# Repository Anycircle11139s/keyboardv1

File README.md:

# keyboardv1
For hack club stasis, I have to journal a lot, and when I journal, I'm locked in, I just keep on typing and typing until I realise that my hands ache like hell because of my uncomfortable keyboard. Because of this, I decided to make myself a customisable 65% keyboard that I can use for playing games (I can customise the keys and make different modes for what I'm doing), journal and all my other typing needs. I created a keyboard matrix for the schematic and placed all my keys into a specific format in the pcb along with making some stablisation holes for space bars and other keycaps. I also added some tuff af silkscreen to the PCB. For the case, I designed a simple, sleek case which surround the keyboard and has no lid. I made it simplistic but added some small design additions so the keyboard wouldn't get to boring. I also added a small slot to the case of my split keyboard which I can use to attach modules whihc I can design in the future. Overall I am really proud of what I made and can't wait to build it irl.

<br>

<br>

<br>

<br>

<br>

<br>

<br>

<br>
<br>
<br>

BOM:
<br>
<br>

|Name                             |Purpose                           |Quantity|Total Cost (USD)|Link                                                                                                                                                                                                                                                                                                                                                                                                                                                                                                                                                                                                                                          |Distributor    |
|---------------------------------|----------------------------------|--------|----------------|----------------------------------------------------------------------------------------------------------------------------------------------------------------------------------------------------------------------------------------------------------------------------------------------------------------------------------------------------------------------------------------------------------------------------------------------------------------------------------------------------------------------------------------------------------------------------------------------------------------------------------------------|---------------|
|case                             |the case for the keyboard         |1       |10.00           |                                                                                                                                                                                                                                                                                                                                                                                                                                                                                                                                                                                                                                              |printing legion|
|PCB                              |the pcb for the board             |1       |27.84           |                                                                                                                                                                                                                                                                                                                                                                                                                                                                                                                                                                                                                                              |jlcpcb         |
|1n4148 diodes                    |the diodes for keyboard matrix    |100     |2.84            |https://www.aliexpress.com/item/1005011766943016.html?spm=a2g0o.productlist.main.7.6b3366c9XO8nET&algo_pvid=4686ff8b-01ef-4d59-aece-2ba6a6420e8b&algo_exp_id=4686ff8b-01ef-4d59-aece-2ba6a6420e8b-6&pdp_ext_f=%7B%22order%22%3A%22159%22%2C%22eval%22%3A%221%22%2C%22fromPage%22%3A%22search%22%7D&pdp_npi=6%40dis%21USD%212.96%212.84%21%21%2120.10%2119.30%21%402101d97817776923407452272e1e3a%2112000056498191665%21sea%21AU%217402515296%21X%211%210%21n_tag%3A-29919%3Bd%3Aef1e07f3%3Bm03_new_user%3A-29895&curPageLogUid=WxqQIHnQBOvN&utparam-url=scene%3Asearch%7Cquery_from%3A%7Cx_object_id%3A1005011766943016%7C_p_origin_prod%3A   |ali express    |
|raspberry pi pico h              |the microconrtoller devboard thing|1       |3.00            |https://www.aliexpress.com/item/1005009844027732.html?spm=a2g0o.productlist.main.13.4827apCCapCCqF&utparam-url=scene%3Asearch%7Cquery_from%3Apc_back_same_best%7Cx_object_id%3A1005009844027732%7C_p_origin_prod%3A&algo_pvid=c51c447d-b00d-4d3c-9df1-87a988eed2e9&algo_exp_id=c51c447d-b00d-4d3c-9df1-87a988eed2e9&pdp_ext_f=%7B%22order%22%3A%221119%22%2C%22fromPage%22%3A%22search%22%7D&pdp_npi=6%40dis%21USD%216.57%212.98%21%21%2144.62%2120.23%21%40210328c017776922501718063e1b4c%2112000050339370579%21sea%21AU%217402515296%21X%211%210%21n_tag%3A-29919%3Bd%3Aef1e07f3%3Bm03_new_user%3A-29895%3BpisId%3A5000000206134117         |ali express    |
|Durock Clear Screw-In Stabilizers|stabilizers for space bar         |1       |7.00            |https://www.aliexpress.com/item/1005007236845004.html?spm=a2g0o.productlist.main.3.1898ase7ase7JM&algo_pvid=5806a8f2-4c32-4dd2-bbc1-282acfa51f49&algo_exp_id=5806a8f2-4c32-4dd2-bbc1-282acfa51f49-2&pdp_ext_f=%7B%22order%22%3A%22126%22%2C%22eval%22%3A%221%22%2C%22fromPage%22%3A%22search%22%7D&pdp_npi=6%40dis%21USD%216.35%216.35%21%21%216.35%216.35%21%402101e81117776932688596724e0a2a%2112000039909995531%21sea%21AU%217402515296%21X%211%210%21n_tag%3A-29919%3Bd%3Aef1e07f3%3Bm03_new_user%3A-29895&curPageLogUid=cq3Hpwq6BscB&utparam-url=scene%3Asearch%7Cquery_from%3A%7Cx_object_id%3A1005007236845004%7C_p_origin_prod%3A     |ali express    |
|blue gradient keycaps            |switch covers                     |1       |16.55           |https://www.aliexpress.com/item/1005009032705520.html?spm=a2g0o.productlist.main.2.7fe21aK91aK965&algo_pvid=6edcfeac-de3a-448c-b303-d10f2607c087&algo_exp_id=6edcfeac-de3a-448c-b303-d10f2607c087-1&pdp_ext_f=%7B%22order%22%3A%2213%22%2C%22eval%22%3A%221%22%2C%22fromPage%22%3A%22search%22%7D&pdp_npi=6%40dis%21USD%2122.07%2116.55%21%21%21149.93%21112.45%21%402101d49617776918006226446e4027%2112000047655880268%21sea%21AU%217402515296%21X%211%210%21n_tag%3A-29919%3Bd%3Aef1e07f3%3Bm03_new_user%3A-29895&curPageLogUid=8Wpnbc57EDZi&utparam-url=scene%3Asearch%7Cquery_from%3A%7Cx_object_id%3A1005009032705520%7C_p_origin_prod%3A|ali express    |
|switches                         |the buttons in keyboard           |90      |35.69           |https://www.aliexpress.com/item/1005009496269008.html?spm=a2g0o.productlist.main.2.7e02fM5MfM5MXw&algo_pvid=59a365f0-2600-4815-a56b-d0a97a5b4dbd&algo_exp_id=59a365f0-2600-4815-a56b-d0a97a5b4dbd-1&pdp_ext_f=%7B%22order%22%3A%22106%22%2C%22eval%22%3A%221%22%2C%22fromPage%22%3A%22search%22%7D&pdp_npi=6%40dis%21USD%2122.99%2119.54%21%21%2122.99%2119.54%21%402101e83017776915737453434ebe85%2112000053392741002%21sea%21AU%217402515296%21X%211%210%21n_tag%3A-29919%3Bd%3Aef1e07f3%3Bm03_new_user%3A-29895&curPageLogUid=lkGMG2pIpivm&utparam-url=scene%3Asearch%7Cquery_from%3A%7Cx_object_id%3A1005009496269008%7C_p_origin_prod%3A |ali express    |

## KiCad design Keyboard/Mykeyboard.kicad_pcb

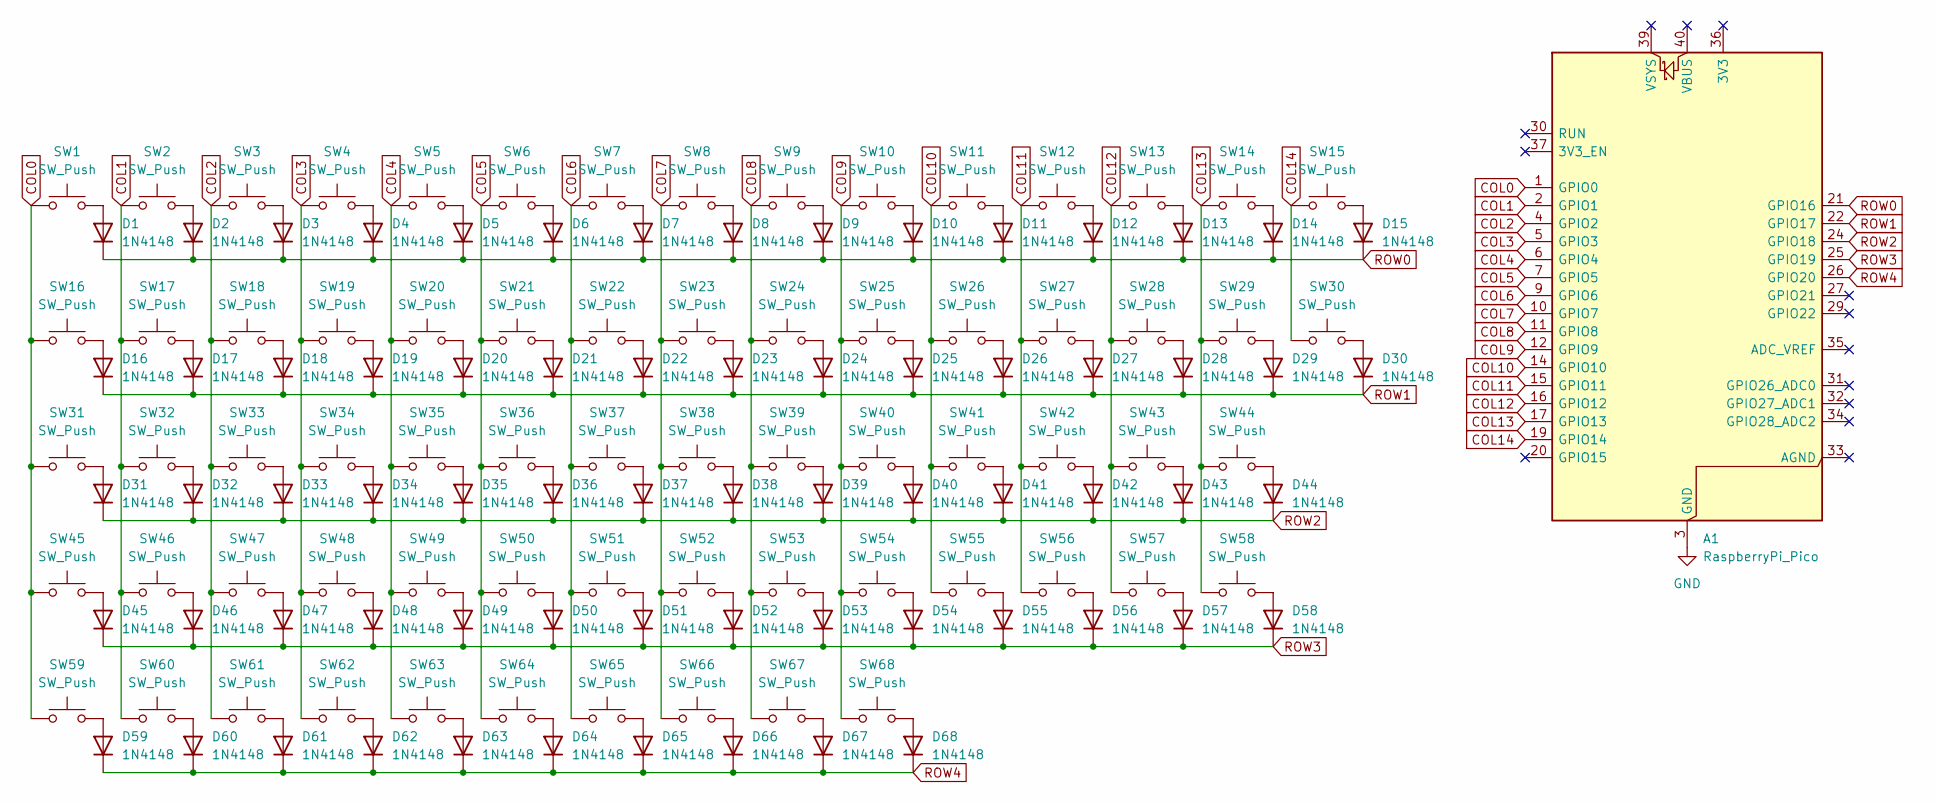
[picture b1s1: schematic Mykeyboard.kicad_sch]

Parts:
A1: RaspberryPi_Pico; RaspberryPi_Pico_Common_Unspecified
D1, D2, D3, D4, D5, D6, D7, D8, D9, D10, D11, D12, D13, D14, D15, D16, D17, D18, D19, D20, D21, D22, D23, D24, D25, D26, D27, D28, D29, D30, D31, D32, D33, D34, D35, D36, D37, D38, D39, D40, D41, D42, D43, D44, D45, D46, D47, D48, D49, D50, D51, D52, D53, D54, D55, D56, D57, D58, D59, D60, D61, D62, D63, D64, D65, D66, D67, D68: 1N4148; D_DO-35_SOD27_P7.62mm_Horizontal
SW1, SW2, SW3, SW4, SW5, SW6, SW7, SW8, SW9, SW10, SW11, SW12, SW13, SW15, SW17, SW18, SW19, SW20, SW21, SW22, SW23, SW24, SW25, SW26, SW27, SW28, SW30, SW32, SW33, SW34, SW35, SW36, SW37, SW38, SW39, SW40, SW41, SW42, SW44, SW46, SW47, SW48, SW49, SW50, SW51, SW52, SW53, SW54, SW55, SW57, SW58, SW63, SW64, SW65, SW66, SW67, SW68: SW_Push; SW_Cherry_MX_1.00u_PCB
SW14: SW_Push; SW_Cherry_MX_2.00u_PCB
SW16, SW29: SW_Push; SW_Cherry_MX_1.50u_PCB
SW31, SW56: SW_Push; SW_Cherry_MX_1.75u_PCB
SW43, SW45: SW_Push; SW_Cherry_MX_2.25u_PCB
SW59, SW60, SW61: SW_Push; SW_Cherry_MX_1.25u_PCB
SW62: SW_Push; SW_Cherry_MX_6.25u_PCB

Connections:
COL0: A1.1 (GPIO0), SW1.1, SW16.1, SW31.1, SW45.1, SW59.1
COL1: A1.2 (GPIO1), SW2.1, SW17.1, SW32.1, SW46.1, SW60.1
COL2: A1.4 (GPIO2), SW3.1, SW18.1, SW33.1, SW47.1, SW61.1
COL3: A1.5 (GPIO3), SW4.1, SW19.1, SW34.1, SW48.1, SW62.1
COL4: A1.6 (GPIO4), SW5.1, SW20.1, SW35.1, SW49.1, SW63.1
COL5: A1.7 (GPIO5), SW6.1, SW21.1, SW36.1, SW50.1, SW64.1
COL6: A1.9 (GPIO6), SW7.1, SW22.1, SW37.1, SW51.1, SW65.1
COL7: A1.10 (GPIO7), SW8.1, SW23.1, SW38.1, SW52.1, SW66.1
COL8: A1.11 (GPIO8), SW9.1, SW24.1, SW39.1, SW53.1, SW67.1
COL9: A1.12 (GPIO9), SW10.1, SW25.1, SW40.1, SW54.1, SW68.1
COL10: A1.14 (GPIO10), SW11.1, SW26.1, SW41.1, SW55.1
COL11: A1.15 (GPIO11), SW12.1, SW27.1, SW42.1, SW56.1
COL12: A1.16 (GPIO12), SW13.1, SW28.1, SW43.1, SW57.1
COL13: A1.17 (GPIO13), SW14.1, SW29.1, SW44.1, SW58.1
COL14: A1.19 (GPIO14), SW15.1, SW30.1
GND: A1.3 (GND), A1.8 (GND), A1.13 (GND), A1.18 (GND), A1.23 (GND), A1.28 (GND), A1.38 (GND)
unnamed: D1.2 (A), SW1.2
unnamed: D2.2 (A), SW2.2
unnamed: D3.2 (A), SW3.2
unnamed: D4.2 (A), SW4.2
unnamed: D5.2 (A), SW5.2
unnamed: D6.2 (A), SW6.2
unnamed: D7.2 (A), SW7.2
unnamed: D8.2 (A), SW8.2
unnamed: D9.2 (A), SW9.2
unnamed: D10.2 (A), SW10.2
unnamed: D11.2 (A), SW11.2
unnamed: D12.2 (A), SW12.2
unnamed: D13.2 (A), SW13.2
unnamed: D14.2 (A), SW14.2
unnamed: D15.2 (A), SW15.2
unnamed: D16.2 (A), SW16.2
unnamed: D17.2 (A), SW17.2
unnamed: D18.2 (A), SW18.2
unnamed: D19.2 (A), SW19.2
unnamed: D20.2 (A), SW20.2
unnamed: D21.2 (A), SW21.2
unnamed: D22.2 (A), SW22.2
unnamed: D23.2 (A), SW23.2
unnamed: D24.2 (A), SW24.2
unnamed: D25.2 (A), SW25.2
unnamed: D26.2 (A), SW26.2
unnamed: D27.2 (A), SW27.2
unnamed: D28.2 (A), SW28.2
unnamed: D29.2 (A), SW29.2
unnamed: D30.2 (A), SW30.2
unnamed: D31.2 (A), SW31.2
unnamed: D32.2 (A), SW32.2
unnamed: D33.2 (A), SW33.2
unnamed: D34.2 (A), SW34.2
unnamed: D35.2 (A), SW35.2
unnamed: D36.2 (A), SW36.2
unnamed: D37.2 (A), SW37.2
unnamed: D38.2 (A), SW38.2
unnamed: D39.2 (A), SW39.2
unnamed: D40.2 (A), SW40.2
unnamed: D41.2 (A), SW41.2
unnamed: D42.2 (A), SW42.2
unnamed: D43.2 (A), SW43.2
unnamed: D44.2 (A), SW44.2
unnamed: D45.2 (A), SW45.2
unnamed: D46.2 (A), SW46.2
unnamed: D47.2 (A), SW47.2
unnamed: D48.2 (A), SW48.2
unnamed: D49.2 (A), SW49.2
unnamed: D50.2 (A), SW50.2
unnamed: D51.2 (A), SW51.2
unnamed: D52.2 (A), SW52.2
unnamed: D53.2 (A), SW53.2
unnamed: D54.2 (A), SW54.2
unnamed: D55.2 (A), SW55.2
unnamed: D56.2 (A), SW56.2
unnamed: D57.2 (A), SW57.2
unnamed: D58.2 (A), SW58.2
unnamed: D59.2 (A), SW59.2
unnamed: D60.2 (A), SW60.2
unnamed: D61.2 (A), SW61.2
unnamed: D62.2 (A), SW62.2
unnamed: D63.2 (A), SW63.2
unnamed: D64.2 (A), SW64.2
unnamed: D65.2 (A), SW65.2
unnamed: D66.2 (A), SW66.2
unnamed: D67.2 (A), SW67.2
unnamed: D68.2 (A), SW68.2
ROW0: A1.21 (GPIO16), D1.1 (K), D2.1 (K), D3.1 (K), D4.1 (K), D5.1 (K), D6.1 (K), D7.1 (K), D8.1 (K), D9.1 (K), D10.1 (K), D11.1 (K), D12.1 (K), D13.1 (K), D14.1 (K), D15.1 (K)
ROW1: A1.22 (GPIO17), D16.1 (K), D17.1 (K), D18.1 (K), D19.1 (K), D20.1 (K), D21.1 (K), D22.1 (K), D23.1 (K), D24.1 (K), D25.1 (K), D26.1 (K), D27.1 (K), D28.1 (K), D29.1 (K), D30.1 (K)
ROW2: A1.24 (GPIO18), D31.1 (K), D32.1 (K), D33.1 (K), D34.1 (K), D35.1 (K), D36.1 (K), D37.1 (K), D38.1 (K), D39.1 (K), D40.1 (K), D41.1 (K), D42.1 (K), D43.1 (K), D44.1 (K)
ROW3: A1.25 (GPIO19), D45.1 (K), D46.1 (K), D47.1 (K), D48.1 (K), D49.1 (K), D50.1 (K), D51.1 (K), D52.1 (K), D53.1 (K), D54.1 (K), D55.1 (K), D56.1 (K), D57.1 (K), D58.1 (K)
ROW4: A1.26 (GPIO20), D59.1 (K), D60.1 (K), D61.1 (K), D62.1 (K), D63.1 (K), D64.1 (K), D65.1 (K), D66.1 (K), D67.1 (K), D68.1 (K)

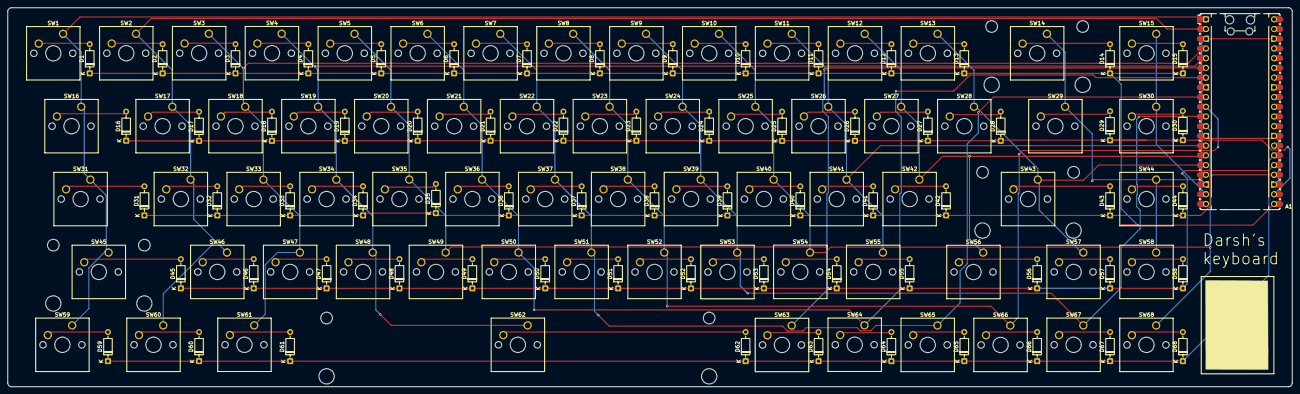
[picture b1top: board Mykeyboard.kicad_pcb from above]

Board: 2 copper layers, 335.8 x 99.1 mm, 137 parts (0 on the bottom side), 89 nets.
